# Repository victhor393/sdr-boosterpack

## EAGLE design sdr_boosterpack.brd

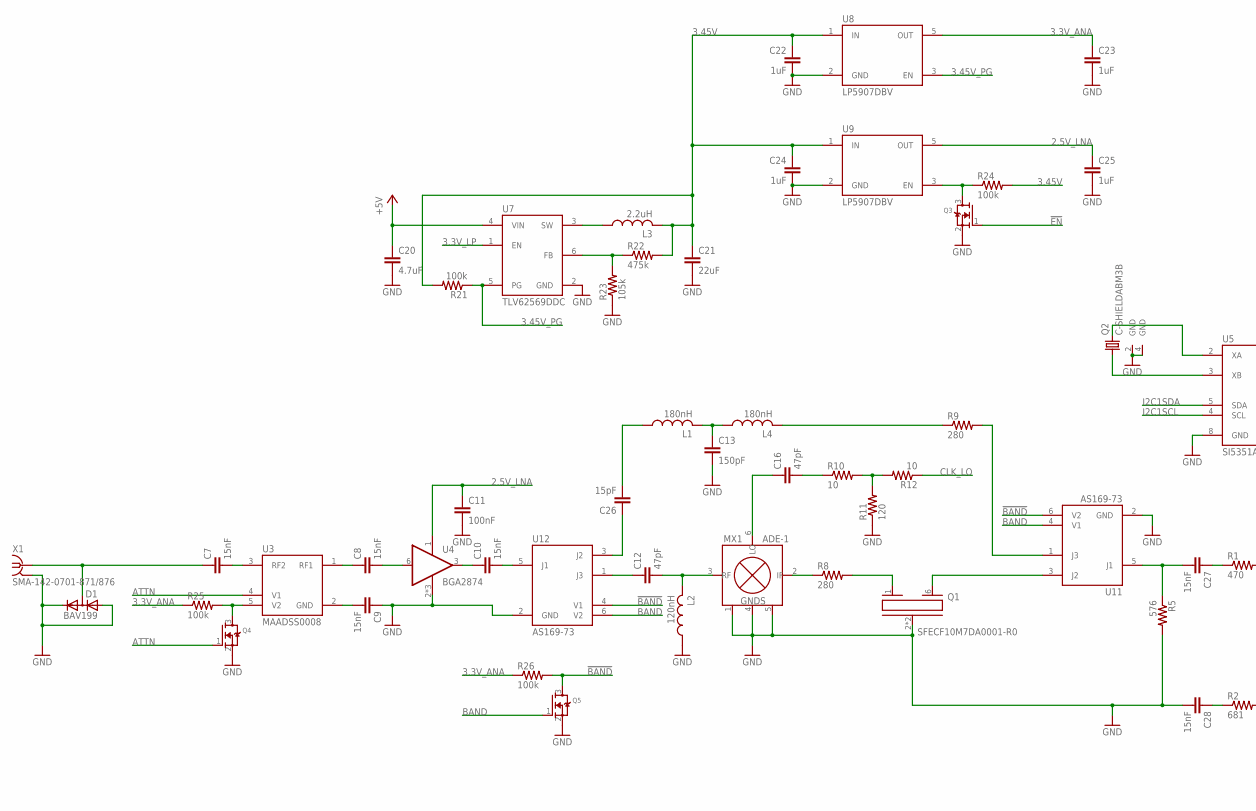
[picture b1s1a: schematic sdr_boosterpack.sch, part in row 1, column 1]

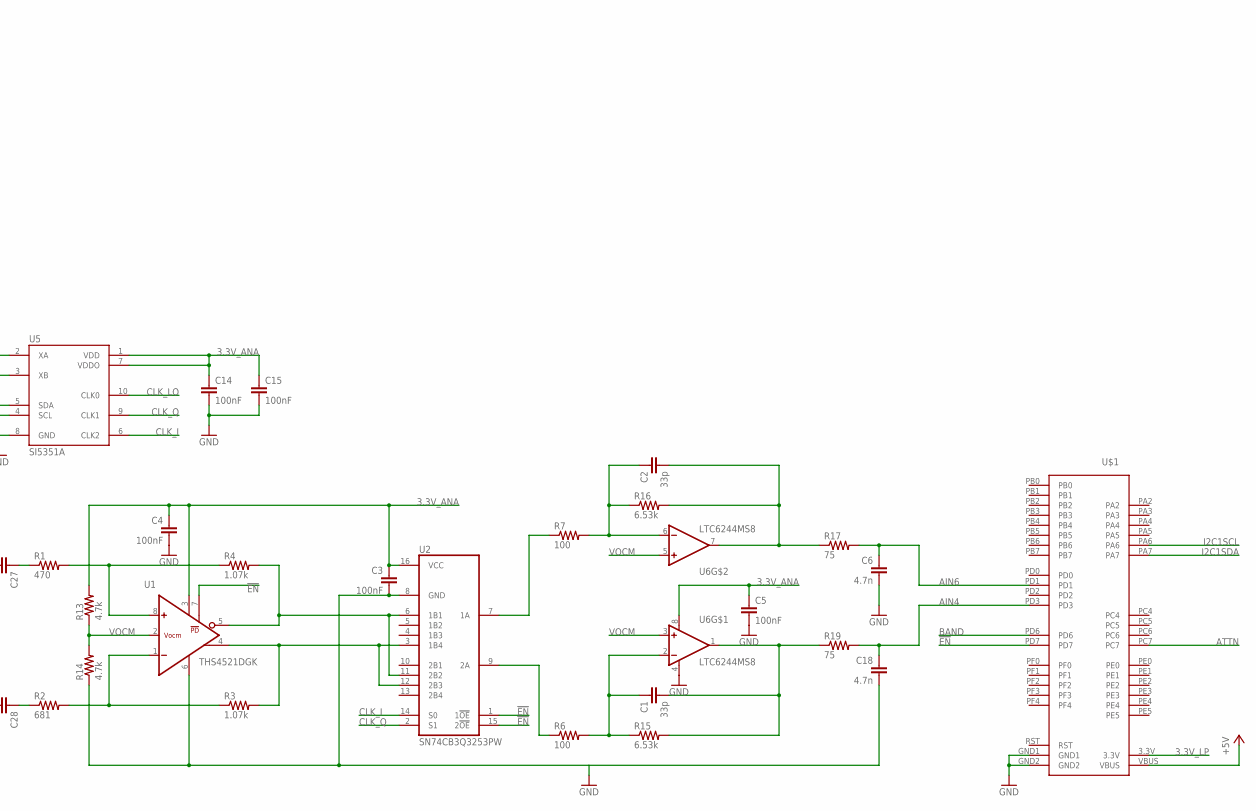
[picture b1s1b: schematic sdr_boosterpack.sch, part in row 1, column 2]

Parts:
C1, C2: 33p; C0603
C3, C4, C5, C11, C14, C15: 100nF; C0603
C6, C18: 4.7n; C0603
C7, C8, C9, C10, C27, C28: 15nF; C0603
C12, C16: 47pF; C0603
C13: 150pF; C0603
C20: 4.7uF; C0805
C21: 22uF; C0805
C22, C23, C24, C25: 1uF; C0805
C26: 15pF; C0603
D1: BAV199; SOT23
L1, L4: 180nH; C0603
L2: 120nH; C0603
L3: 2.2uH; XAL4040
MX1: ADE-1; CD636
Q1: SFECF10M7DA0001-R0; SFECF
Q2: C-SHIELDABM3B; ABM3B
Q3, Q4, Q5: MOSFET-NREFLOW; SOT23
R1: 470; R0603
R2: 681; R0603
R3, R4: 1.07k; R0603
R5: 576; R0603
R6, R7: 100; R0603
R8, R9: 280; R0603
R10, R12: 10; R0603
R11: 120; R0603
R13, R14: 4.7k; R0603
R15, R16: 6.53k; R0603
R17, R19: 75; R0603
R21, R24, R25, R26: 100k; R0603
R22: 475k; R0603
R23: 105k; R0603
U1: THS4521DGK; DGK_S-PDSO-G8
U2: SN74CB3Q3253PW; PW_R-PDSO-G16
U3: MAADSS0008; SOT23-5L
U4: BGA2874; SOT363_PHILIPS
U5: SI5351A; MSOP10
U6: LTC6244MS8; MSOP8
U7: TLV62569DDC; SOT23-6
U8, U9: LP5907DBV; MF05A-M
U11, U12: AS169-73; SOT23-6
U$1: STELLARIS-LAUNCHPADSTELLARIS-LAUNCHPAD-XL-HALF-LE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; LAUNCHPAD-XL-HALF-LENGTH
X1: SMA-142-0701-871/876; J502-ND-142-0701-871/876

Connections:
2.5V_LNA: C11.1, C25.1, U4.1 (V+), U9.5 (OUT)
3.3V_ANA: C3.1, C4.1, C5.1, C14.1, C15.1, C23.1, R13.2, R25.1, R26.1, U1.3 (V+), U2.16 (VCC), U5.1 (VDD), U5.7 (VDDO), U6.8 (V+), U8.5 (OUT)
3.3V_LP: U7.1 (EN), U$1.3.3V
3.45V: C21.1, C22.1, C24.1, L3.2, R21.2, R22.2, R24.2, U8.1 (IN), U9.1 (IN)
3.45V_PG: R21.1, U7.5 (PG), U8.3 (EN)
!BAND: Q5.3 (D), R26.2, U11.6 (V2), U12.4 (V1)
!EN: Q3.1 (G), U1.7 (PD), U2.1 (1!OE), U2.15 (2!OE), U$1.PD7
+5V: C20.1, U7.4 (VIN), U$1.VBUS
AIN4: C18.1, R19.2, U$1.PD3
AIN6: C6.1, R17.2, U$1.PD1
ATTN: Q4.1 (G), U3.4 (V1), U$1.PC7
BAND: Q5.1 (G), U11.4 (V1), U12.6 (V2), U$1.PD6
CLK_I: U2.14 (S0), U5.6 (CLK2)
CLK_LO: R12.1, U5.10 (CLK0)
CLK_Q: U2.2 (S1), U5.9 (CLK1)
GND: C3.2, C4.2, C5.2, C6.2, C9.1, C11.2, C13.2, C14.2, C15.2, C18.2, C20.2, C21.2, C22.2, C23.2, C24.2, C25.2, C28.2, D1.1 (A), D1.2 (C), L2.1, MX1.1 (GND), MX1.4 (GND), MX1.5 (GND), Q1.2 (GND), Q1.5 (GND), Q2.2 (GND), Q2.4 (GND), Q3.2 (S), Q4.2 (S), Q5.2 (S), R5.2, R11.1, R14.1, R23.1, U1.6 (V-), U2.8 (GND), U4.2 (V-), U4.4 (V-), U4.5 (V-), U5.8 (GND), U6.4 (V-), U7.2 (GND), U8.2 (GND), U9.2 (GND), U11.2 (GND), U12.2 (GND), U$1.GND1, U$1.GND2, X1.G@1 (2), X1.G@2 (2), X1.G@3 (2), X1.G@4 (2)
I2C1SCL: U5.4 (SCL), U$1.PA6
I2C1SDA: U5.5 (SDA), U$1.PA7
unnamed: R1.2, R4.1, U1.8 (+IN)
unnamed: Q4.3 (D), R25.2, U3.5 (V2)
unnamed: R2.2, R3.1, U1.1 (-IN)
unnamed: C1.1, R6.2, R15.1, U6.2 (-IN)
unnamed: C27.1, R1.1
unnamed: R4.2, U1.5 (-OUT), U2.6 (1B1), U2.11 (2B2)
unnamed: Q1.6 (OUT), U11.3 (J2)
unnamed: C2.2, R16.2, R17.1, U6.7 (OUT)
unnamed: R6.1, U2.9 (2A)
unnamed: C8.2, U4.6 (-IN)
unnamed: R3.2, U1.4 (+OUT), U2.3 (1B4), U2.12 (2B3)
unnamed: R7.1, U2.7 (1A)
unnamed: C26.2, L1.1
unnamed: C9.2, U3.2 (GND)
unnamed: C7.1, D1.3 (AC), X1.1
unnamed: C10.2, U12.5 (J1)
unnamed: C7.2, U3.3 (RF2)
unnamed: C8.1, U3.1 (RF1)
unnamed: C10.1, U4.3 (OUT)
unnamed: C12.1, U12.1 (J3)
unnamed: L4.2, R9.1
unnamed: MX1.2 (IF), R8.1
unnamed: Q1.1 (IN), R8.2
unnamed: R9.2, U11.1 (J3)
unnamed: C13.1, L1.2, L4.1
unnamed: C12.2, L2.2, MX1.3 (RF)
unnamed: C16.2, R10.1
unnamed: R10.2, R11.2, R12.2
unnamed: C16.1, MX1.6 (LO)
unnamed: C2.1, R7.2, R16.1, U6.6 (-IN)
unnamed: C1.2, R15.2, R19.1, U6.1 (OUT)
unnamed: Q2.3 (2), U5.2 (XA)
unnamed: Q2.1, U5.3 (XB)
unnamed: L3.1, U7.3 (SW)
unnamed: C26.1, U12.3 (J2)
unnamed: C28.1, R2.1
unnamed: R22.1, R23.2, U7.6 (FB)
unnamed: C27.2, R5.1, U11.5 (J1)
unnamed: Q3.3 (D), R24.1, U9.3 (EN)
RST: U$1.RST
VOCM: R13.1, R14.2, U1.2 (VOCM), U6.3 (+IN), U6.5 (+IN)

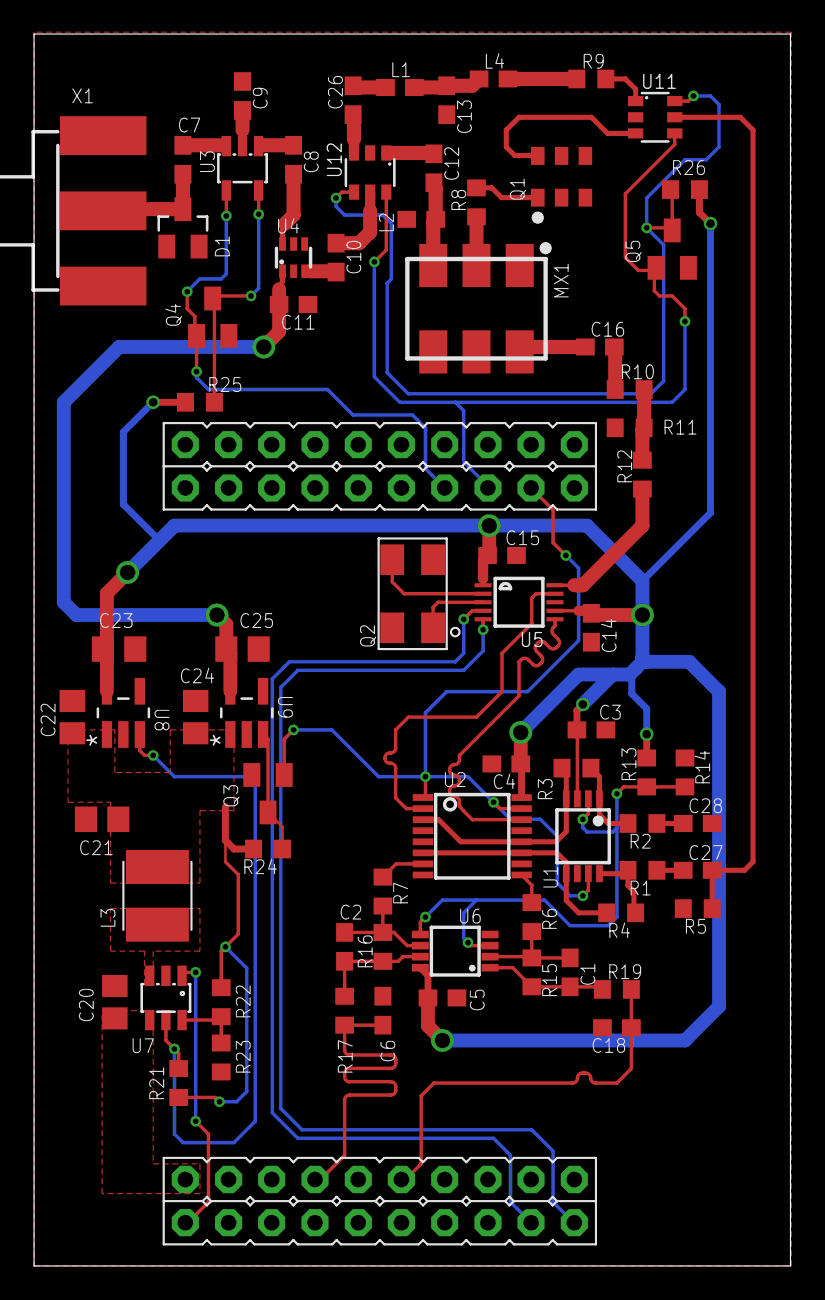
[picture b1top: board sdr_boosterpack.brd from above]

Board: 2 copper layers, 44.5 x 72.4 mm, 74 parts (0 on the bottom side), 58 nets.

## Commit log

2019-05-21 Added schematic and board layout in pdf format
